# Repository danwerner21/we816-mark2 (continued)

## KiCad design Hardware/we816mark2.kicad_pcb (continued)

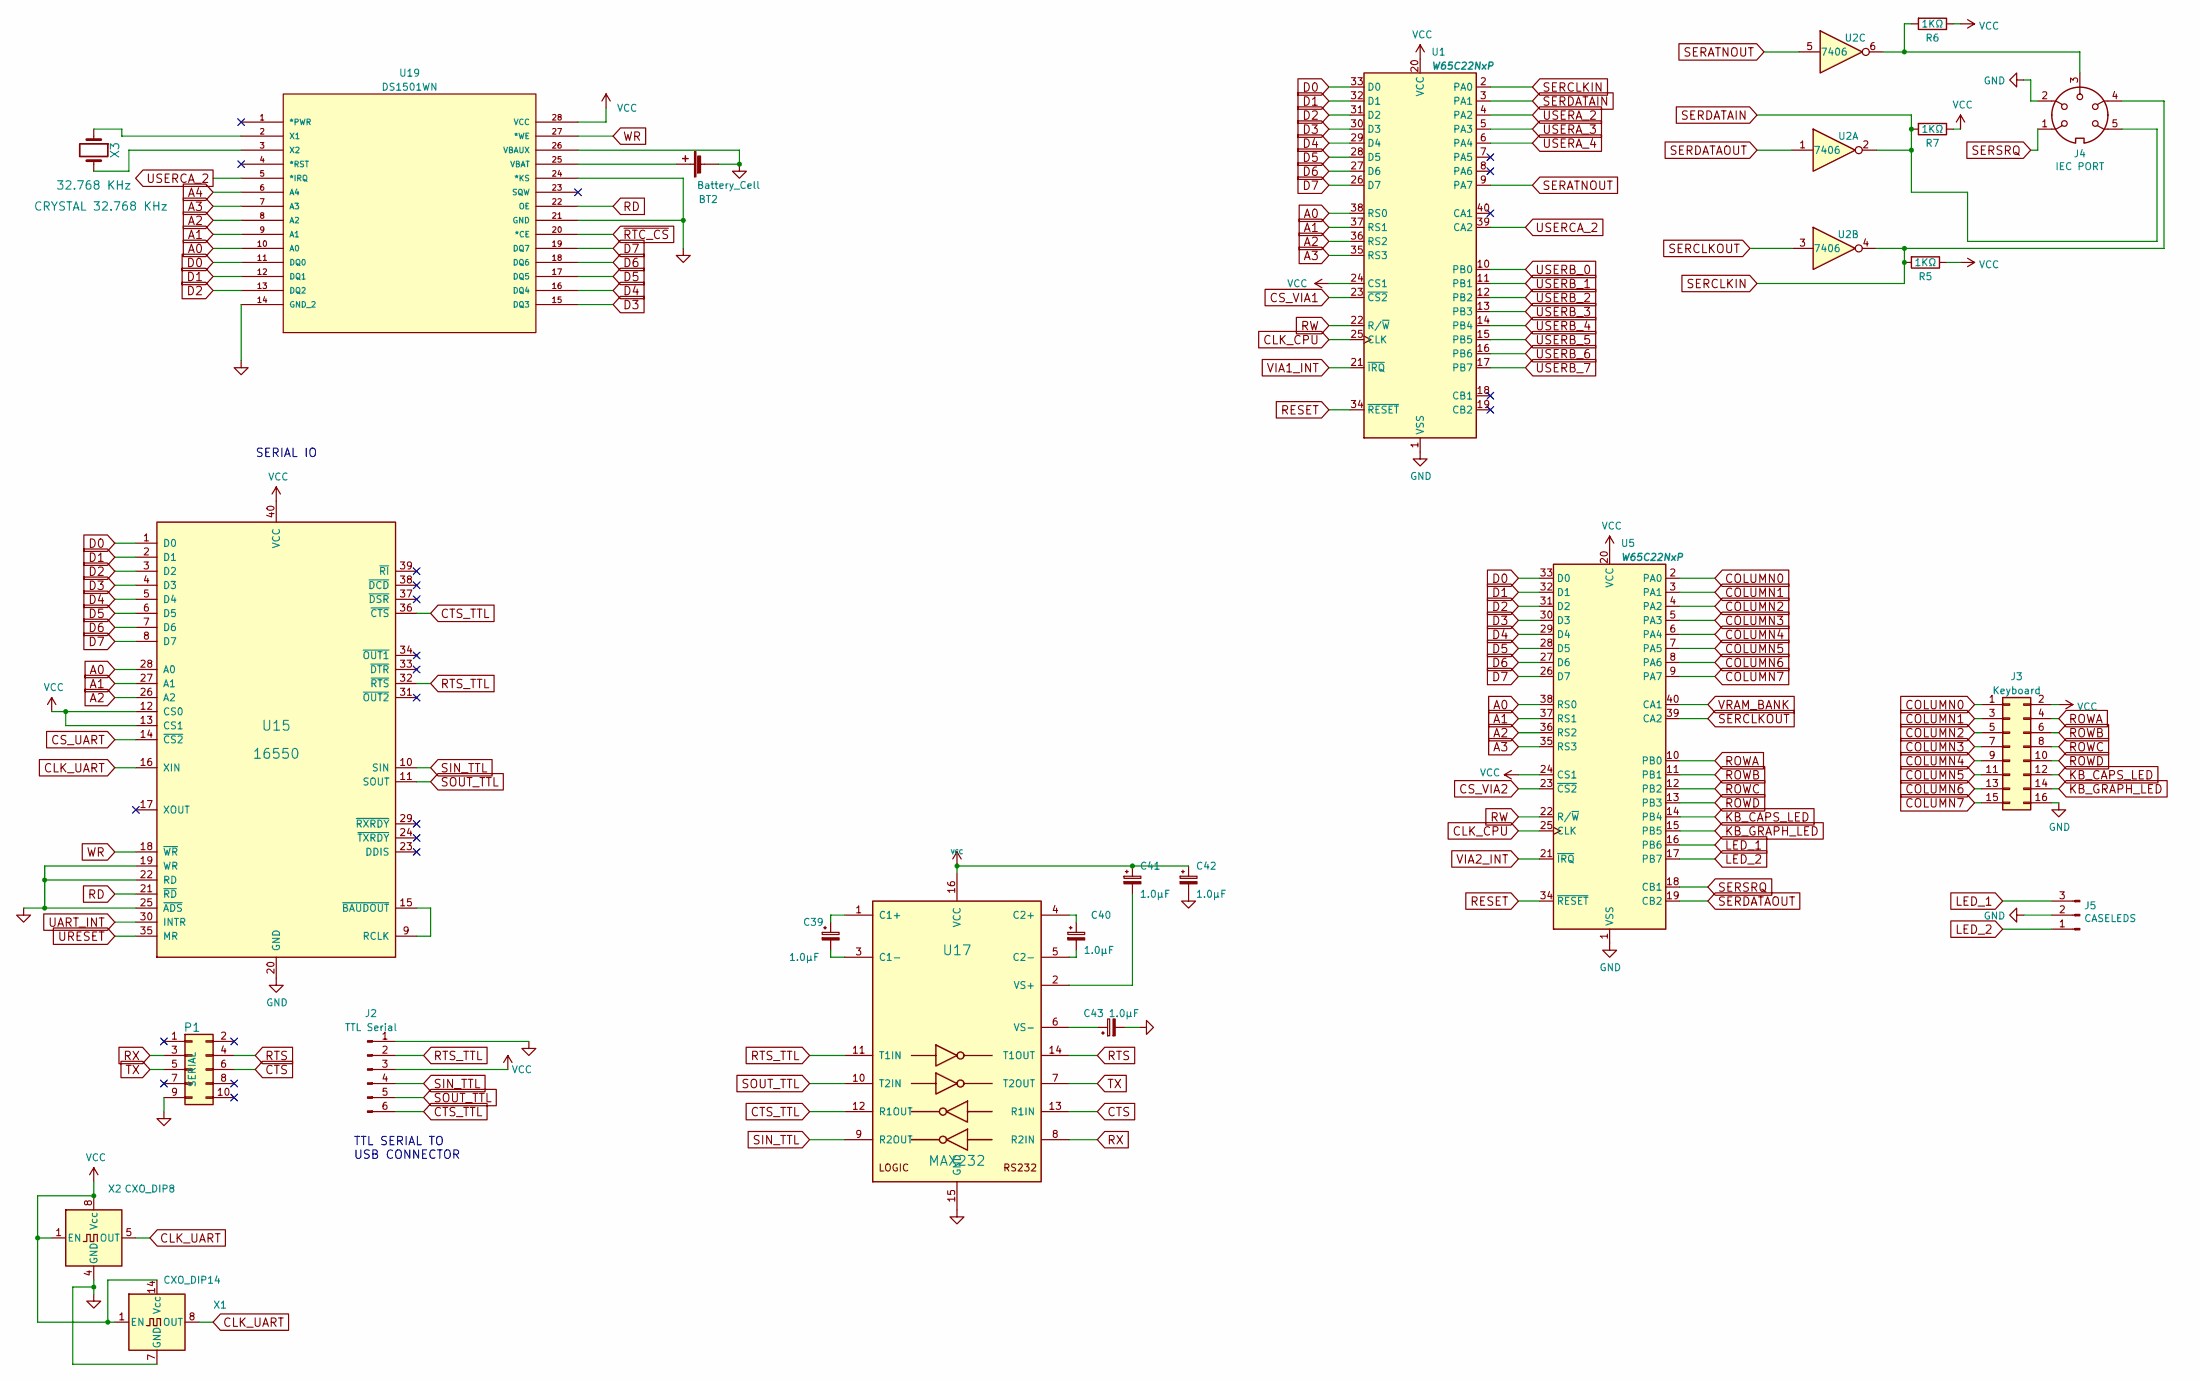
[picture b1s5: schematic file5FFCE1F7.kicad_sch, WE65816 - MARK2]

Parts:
BT2: Battery_Cell; Battery_Holder_Coin_2032_BS-7_FIXED
C39, C40, C41, C42, C43: 1.0µF; CP_Radial_D4.0mm_P2.00mm
J2: TTL Serial; PinHeader_1x06_P2.54mm_Vertical
J3: Keyboard; PinHeader_2x08_P2.54mm_Vertical
J4: IEC PORT; din6
J5: CASELEDS; PinHeader_1x03_P2.54mm_Vertical
P1: SERIAL; PinHeader_2x05_P2.54mm_Vertical
R5, R6, R7: 1KΩ; R_Axial_DIN0204_L3.6mm_D1.6mm_P5.08mm_Horizontal
U1, U5: W65C22NxP; DIP-40_W15.24mm_Socket_LongPads
U2: 7406; DIP-14_W7.62mm_Socket_LongPads
U15: 16550; DIP-40_W15.24mm_Socket_LongPads
U17: MAX232; DIP-16_W7.62mm_Socket_LongPads
U19: DS1501WN; DIP-28_W15.24mm_Socket_LongPads; MANUFACTURER_PART_NUMBER DS1501WN+
X1: CXO_DIP14; Oscillator_DIP-14
X2: CXO_DIP8; Oscillator_DIP-8
X3: CRYSTAL 32.768 KHz; Crystal_Round_D1.5mm_Vertical

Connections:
A0: U1.38 (RS0), U5.38 (RS0), U15.28 (A0), U19.10 (A0); also elsewhere on the board
A1: U1.37 (RS1), U5.37 (RS1), U15.27 (A1), U19.9 (A1); also elsewhere on the board
A2: U1.36 (RS2), U5.36 (RS2), U15.26 (A2), U19.8 (A2); also elsewhere on the board
A3: U1.35 (RS3), U5.35 (RS3), U19.7 (A3); also elsewhere on the board
A4: U19.6 (A4); also elsewhere on the board
COLUMN0: J3.1, U5.2 (PA0)
COLUMN1: J3.3, U5.3 (PA1)
COLUMN2: J3.5, U5.4 (PA2)
COLUMN3: J3.7, U5.5 (PA3)
COLUMN4: J3.9, U5.6 (PA4)
COLUMN5: J3.11, U5.7 (PA5)
COLUMN6: J3.13, U5.8 (PA6)
COLUMN7: J3.15, U5.9 (PA7)
CS_UART: U15.14 (~CS2); also elsewhere on the board
CS_VIA1: U1.23 (~CS2); also elsewhere on the board
CS_VIA2: U5.23 (~CS2); also elsewhere on the board
CTS: P1.6, U17.13 (R1IN)
CTS_TTL: J2.6, U15.36 (~CTS), U17.12 (R1OUT)
D0: U1.33 (D0), U5.33 (D0), U15.1 (D0), U19.11 (DQ0); also elsewhere on the board
D1: U1.32 (D1), U5.32 (D1), U15.2 (D1), U19.12 (DQ1); also elsewhere on the board
D2: U1.31 (D2), U5.31 (D2), U15.3 (D2), U19.13 (DQ2); also elsewhere on the board
D3: U1.30 (D3), U5.30 (D3), U15.4 (D3), U19.15 (DQ3); also elsewhere on the board
D4: U1.29 (D4), U5.29 (D4), U15.5 (D4), U19.16 (DQ4); also elsewhere on the board
D5: U1.28 (D5), U5.28 (D5), U15.6 (D5), U19.17 (DQ5); also elsewhere on the board
D6: U1.27 (D6), U5.27 (D6), U15.7 (D6), U19.18 (DQ6); also elsewhere on the board
D7: U1.26 (D7), U5.26 (D7), U15.8 (D7), U19.19 (DQ7); also elsewhere on the board
GND: BT2.2 (-), C42.2, C43.2, J2.1, J3.16, J4.2, J5.2, P1.9, U1.1 (VSS), U5.1 (VSS), U15.19 (WR), U15.20 (GND), U15.22 (RD), U15.25 (~ADS), U17.15 (GND), U19.14 (GND_2), U19.21 (GND), U19.24 (*KS), U19.26 (VBAUX), X1.7 (GND), X2.4 (GND); also elsewhere on the board
KB_CAPS_LED: J3.12, U5.14 (PB4)
KB_GRAPH_LED: J3.14, U5.15 (PB5)
LED_1: J5.3, U5.16 (PB6)
LED_2: J5.1, U5.17 (PB7)
unnamed: BT2.1 (+), U19.25 (VBAT)
unnamed: J4.3, R6.2, U2.6
unnamed: U15.9 (RCLK), U15.15 (~BAUDOUT)
unnamed: C39.1, U17.1 (C1+)
unnamed: C39.2, U17.3 (C1-)
unnamed: C40.1, U17.4 (C2+)
unnamed: C40.2, U17.5 (C2-)
unnamed: C41.2, U17.2 (VS+)
unnamed: C43.1, U17.6 (VS-)
unnamed: U19.2 (X1), X3.1
unnamed: U19.3 (X2), X3.2
RD: U15.21 (~RD), U19.22 (OE); also elsewhere on the board
RESET: U1.34 (~RESET), U5.34 (~RESET); also elsewhere on the board
ROWA: J3.4, U5.10 (PB0)
ROWB: J3.6, U5.11 (PB1)
ROWC: J3.8, U5.12 (PB2)
ROWD: J3.10, U5.13 (PB3)
RTS: P1.4, U17.14 (T1OUT)
RTS_TTL: J2.2, U15.32 (~RTS), U17.11 (T1IN)
RW: U1.22 (R/~W), U5.22 (R/~W); also elsewhere on the board
RX: P1.3, U17.8 (R2IN)
SERATNOUT: U1.9 (PA7), U2.5
SERCLKIN: J4.4, R5.2, U1.2 (PA0), U2.4
SERCLKOUT: U2.3, U5.39 (CA2)
SERDATAIN: J4.5, R7.2, U1.3 (PA1), U2.2
SERDATAOUT: U2.1, U5.19 (CB2)
SERSRQ: J4.1, U5.18 (CB1)
SIN_TTL: J2.4, U15.10 (SIN), U17.9 (R2OUT)
SOUT_TTL: J2.5, U15.11 (SOUT), U17.10 (T2IN)
TX: P1.5, U17.7 (T2OUT)
UART_INT: U15.30 (INTR); also elsewhere on the board
URESET: U15.35 (MR); also elsewhere on the board
USERA_2: U1.4 (PA2); also elsewhere on the board
USERA_3: U1.5 (PA3); also elsewhere on the board
USERA_4: U1.6 (PA4); also elsewhere on the board
USERB_0: U1.10 (PB0); also elsewhere on the board
USERB_1: U1.11 (PB1); also elsewhere on the board
USERB_2: U1.12 (PB2); also elsewhere on the board
USERB_3: U1.13 (PB3); also elsewhere on the board
USERB_4: U1.14 (PB4); also elsewhere on the board
USERB_5: U1.15 (PB5); also elsewhere on the board
USERB_6: U1.16 (PB6); also elsewhere on the board
USERB_7: U1.17 (PB7); also elsewhere on the board
USERCA_2: U1.39 (CA2), U19.5 (*IRQ)
VCC: C41.1, C42.1, J2.3, J3.2, R5.1, R6.1, R7.1, U1.20 (VCC), U1.24 (CS1), U5.20 (VCC), U5.24 (CS1), U15.12 (CS0), U15.13 (CS1), U15.40 (VCC), U17.16 (VCC), U19.28 (VCC), X1.1 (EN), X1.14 (Vcc), X2.1 (EN), X2.8 (Vcc); also elsewhere on the board
VIA1_INT: U1.21 (~IRQ); also elsewhere on the board
VIA2_INT: U5.21 (~IRQ); also elsewhere on the board
VRAM_BANK: U5.40 (CA1); also elsewhere on the board
WR: U15.18 (~WR), U19.27 (*WE); also elsewhere on the board
~RTC_CS: U19.20 (*CE); also elsewhere on the board

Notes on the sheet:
TTL SERIAL TO USB CONNECTOR
SERIAL IO

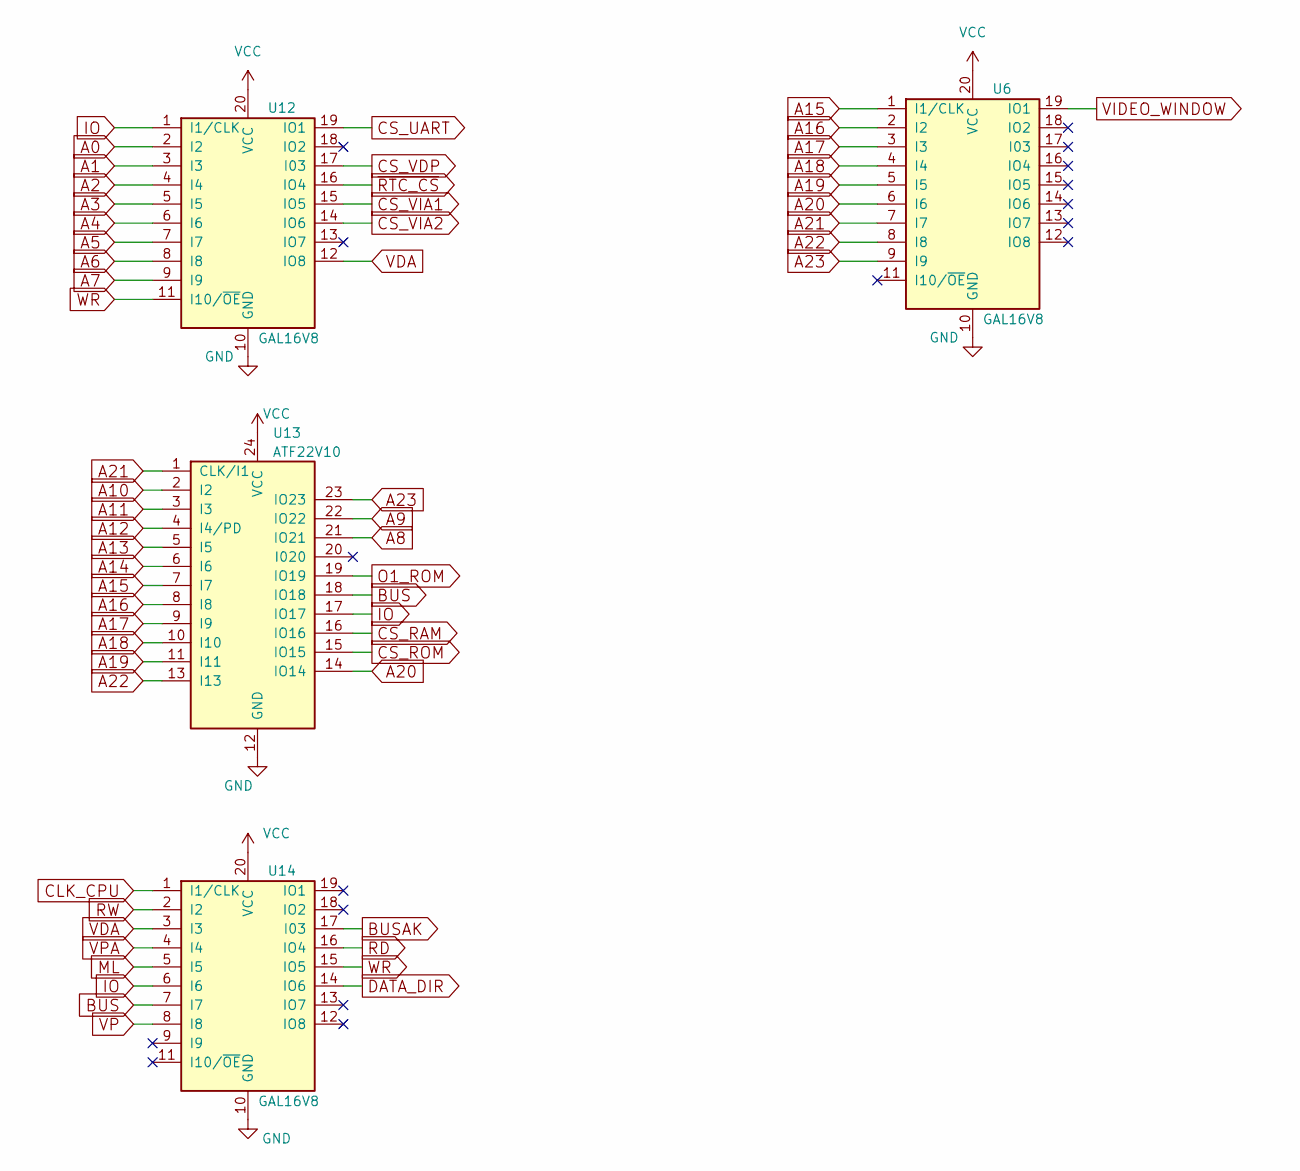
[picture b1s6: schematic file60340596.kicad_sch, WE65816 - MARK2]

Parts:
U6, U12, U14: GAL16V8; DIP-20_W7.62mm_Socket_LongPads
U13: ATF22V10; DIP-24_W7.62mm_Socket_LongPads

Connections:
A0: U12.2 (I2); also elsewhere on the board
A1: U12.3 (I3); also elsewhere on the board
A2: U12.4 (I4); also elsewhere on the board
A3: U12.5 (I5); also elsewhere on the board
A4: U12.6 (I6); also elsewhere on the board
A5: U12.7 (I7); also elsewhere on the board
A6: U12.8 (I8); also elsewhere on the board
A7: U12.9 (I9); also elsewhere on the board
A8: U13.21 (IO21); also elsewhere on the board
A9: U13.22 (IO22); also elsewhere on the board
A10: U13.2 (I2); also elsewhere on the board
A11: U13.3 (I3); also elsewhere on the board
A12: U13.4 (I4/PD); also elsewhere on the board
A13: U13.5 (I5); also elsewhere on the board
A14: U13.6 (I6); also elsewhere on the board
A15: U6.1 (I1/CLK), U13.7 (I7); also elsewhere on the board
A16: U6.2 (I2), U13.8 (I8); also elsewhere on the board
A17: U6.3 (I3), U13.9 (I9); also elsewhere on the board
A18: U6.4 (I4), U13.10 (I10); also elsewhere on the board
A19: U6.5 (I5), U13.11 (I11); also elsewhere on the board
A20: U6.6 (I6), U13.14 (IO14); also elsewhere on the board
A21: U6.7 (I7), U13.1 (CLK/I1); also elsewhere on the board
A22: U6.8 (I8), U13.13 (I13); also elsewhere on the board
A23: U6.9 (I9), U13.23 (IO23); also elsewhere on the board
BUS: U13.18 (IO18), U14.7 (I7)
BUSAK: U14.17 (I03); also elsewhere on the board
CS_RAM: U13.16 (IO16); also elsewhere on the board
CS_ROM: U13.15 (IO15); also elsewhere on the board
CS_UART: U12.19 (IO1); also elsewhere on the board
CS_VDP: U12.17 (I03); also elsewhere on the board
CS_VIA1: U12.15 (IO5); also elsewhere on the board
CS_VIA2: U12.14 (IO6); also elsewhere on the board
DATA_DIR: U14.14 (IO6); also elsewhere on the board
GND: U6.10 (GND), U12.10 (GND), U13.12 (GND), U14.10 (GND); also elsewhere on the board
IO: U12.1 (I1/CLK), U13.17 (IO17), U14.6 (I6)
ML: U14.5 (I5); also elsewhere on the board
O1_ROM: U13.19 (IO19); also elsewhere on the board
RD: U14.16 (IO4); also elsewhere on the board
RW: U14.2 (I2); also elsewhere on the board
VCC: U6.20 (VCC), U12.20 (VCC), U13.24 (VCC), U14.20 (VCC); also elsewhere on the board
VDA: U12.12 (IO8), U14.3 (I3); also elsewhere on the board
VIDEO_WINDOW: U6.19 (IO1); also elsewhere on the board
VP: U14.8 (I8); also elsewhere on the board
VPA: U14.4 (I4); also elsewhere on the board
WR: U12.11 (I10/~OE), U14.15 (IO5); also elsewhere on the board
~RTC_CS: U12.16 (IO4); also elsewhere on the board

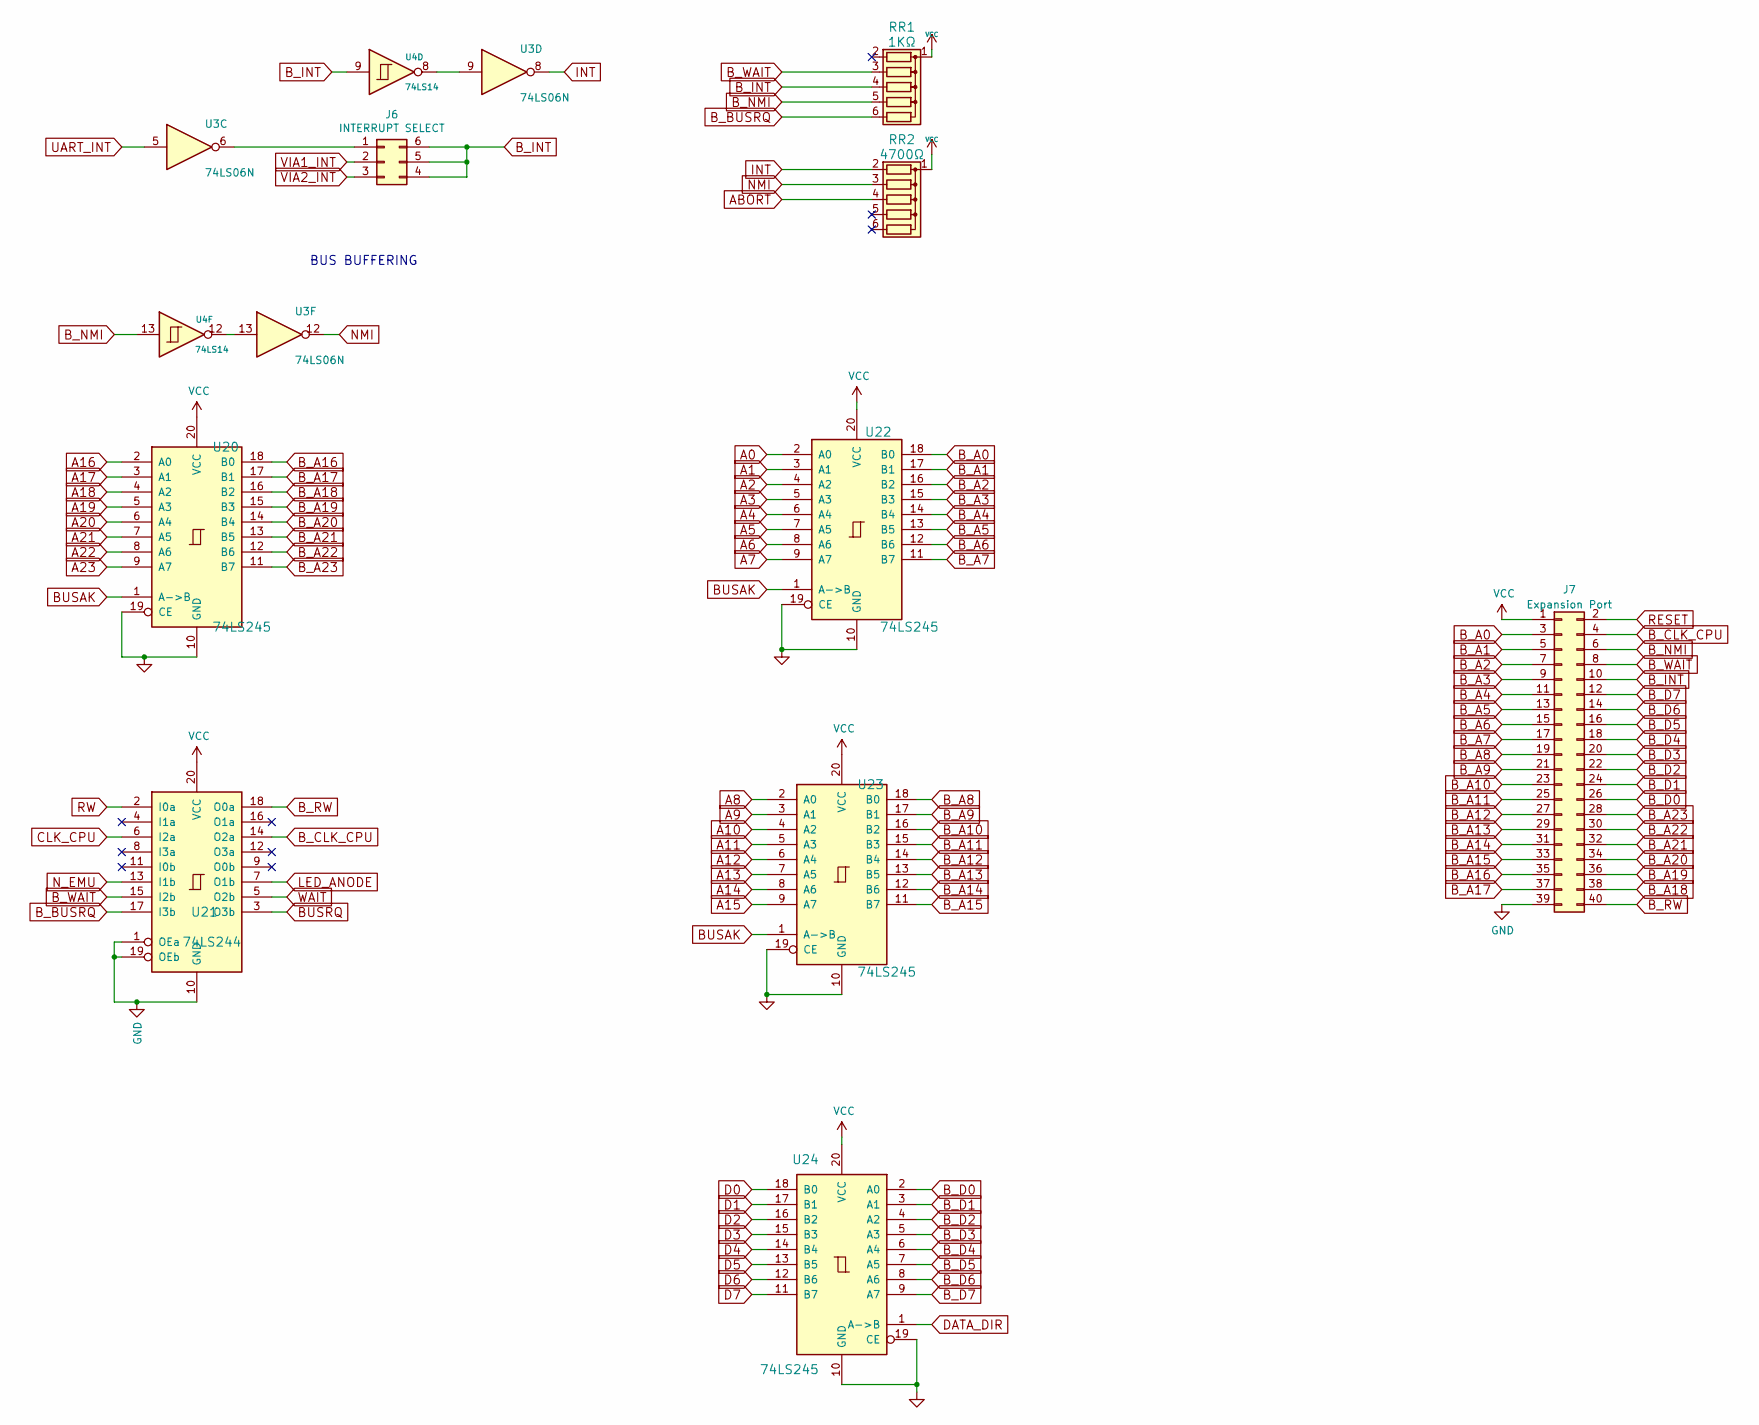
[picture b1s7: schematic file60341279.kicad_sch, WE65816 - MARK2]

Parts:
J6: INTERRUPT SELECT; PinHeader_2x04_P2.54mm_Vertical
J7: Expansion Port; PinSocket_2x20_P2.54mm_Horizontal
RR1: 1KΩ; R_Array_SIP6
RR2: 4700Ω; R_Array_SIP6
U3: 74LS06N; DIP-14_W7.62mm_Socket_LongPads
U4: 74LS14; DIP-14_W7.62mm_Socket_LongPads
U20, U22, U23, U24: 74LS245; DIP-20_W7.62mm_Socket_LongPads
U21: 74LS244; DIP-20_W7.62mm_Socket_LongPads

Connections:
A0: U22.2 (A0); also elsewhere on the board
A1: U22.3 (A1); also elsewhere on the board
A2: U22.4 (A2); also elsewhere on the board
A3: U22.5 (A3); also elsewhere on the board
A4: U22.6 (A4); also elsewhere on the board
A5: U22.7 (A5); also elsewhere on the board
A6: U22.8 (A6); also elsewhere on the board
A7: U22.9 (A7); also elsewhere on the board
A8: U23.2 (A0); also elsewhere on the board
A9: U23.3 (A1); also elsewhere on the board
A10: U23.4 (A2); also elsewhere on the board
A11: U23.5 (A3); also elsewhere on the board
A12: U23.6 (A4); also elsewhere on the board
A13: U23.7 (A5); also elsewhere on the board
A14: U23.8 (A6); also elsewhere on the board
A15: U23.9 (A7); also elsewhere on the board
A16: U20.2 (A0); also elsewhere on the board
A17: U20.3 (A1); also elsewhere on the board
A18: U20.4 (A2); also elsewhere on the board
A19: U20.5 (A3); also elsewhere on the board
A20: U20.6 (A4); also elsewhere on the board
A21: U20.7 (A5); also elsewhere on the board
A22: U20.8 (A6); also elsewhere on the board
A23: U20.9 (A7); also elsewhere on the board
ABORT: RR2.4 (R3); also elsewhere on the board
BUSAK: U20.1 (A->B), U22.1 (A->B), U23.1 (A->B); also elsewhere on the board
BUSRQ: U21.3 (O3b); also elsewhere on the board
B_A0: J7.3, U22.18 (B0)
B_A1: J7.5, U22.17 (B1)
B_A2: J7.7, U22.16 (B2)
B_A3: J7.9, U22.15 (B3)
B_A4: J7.11, U22.14 (B4)
B_A5: J7.13, U22.13 (B5)
B_A6: J7.15, U22.12 (B6)
B_A7: J7.17, U22.11 (B7)
B_A8: J7.19, U23.18 (B0)
B_A9: J7.21, U23.17 (B1)
B_A10: J7.23, U23.16 (B2)
B_A11: J7.25, U23.15 (B3)
B_A12: J7.27, U23.14 (B4)
B_A13: J7.29, U23.13 (B5)
B_A14: J7.31, U23.12 (B6)
B_A15: J7.33, U23.11 (B7)
B_A16: J7.35, U20.18 (B0)
B_A17: J7.37, U20.17 (B1)
B_A18: J7.38, U20.16 (B2)
B_A19: J7.36, U20.15 (B3)
B_A20: J7.34, U20.14 (B4)
B_A21: J7.32, U20.13 (B5)
B_A22: J7.30, U20.12 (B6)
B_A23: J7.28, U20.11 (B7)
B_BUSRQ: RR1.6 (R5), U21.17 (I3b)
B_CLK_CPU: J7.4, U21.14 (O2a)
B_D0: J7.26, U24.2 (A0)
B_D1: J7.24, U24.3 (A1)
B_D2: J7.22, U24.4 (A2)
B_D3: J7.20, U24.5 (A3)
B_D4: J7.18, U24.6 (A4)
B_D5: J7.16, U24.7 (A5)
B_D6: J7.14, U24.8 (A6)
B_D7: J7.12, U24.9 (A7)
B_INT: J6.4, J6.5, J6.6, J7.10, RR1.4 (R3), U4.9
B_NMI: J7.6, RR1.5 (R4), U4.13
B_RW: J7.40, U21.18 (O0a)
B_WAIT: J7.8, RR1.3 (R2), U21.15 (I2b)
D0: U24.18 (B0); also elsewhere on the board
D1: U24.17 (B1); also elsewhere on the board
D2: U24.16 (B2); also elsewhere on the board
D3: U24.15 (B3); also elsewhere on the board
D4: U24.14 (B4); also elsewhere on the board
D5: U24.13 (B5); also elsewhere on the board
D6: U24.12 (B6); also elsewhere on the board
D7: U24.11 (B7); also elsewhere on the board
DATA_DIR: U24.1 (A->B); also elsewhere on the board
GND: J7.39, U20.10 (GND), U20.19 (CE), U21.1 (OEa), U21.10 (GND), U21.19 (OEb), U22.10 (GND), U22.19 (CE), U23.10 (GND), U23.19 (CE), U24.10 (GND), U24.19 (CE); also elsewhere on the board
INT: RR2.2 (R1), U3.8; also elsewhere on the board
LED_ANODE: U21.7 (O1b); also elsewhere on the board
NMI: RR2.3 (R2), U3.12; also elsewhere on the board
N_EMU: U21.13 (I1b); also elsewhere on the board
unnamed: J6.1, U3.6
unnamed: U3.9, U4.8
unnamed: U3.13, U4.12
RESET: J7.2; also elsewhere on the board
RW: U21.2 (I0a); also elsewhere on the board
UART_INT: U3.5; also elsewhere on the board
VCC: J7.1, RR1.1 (common), RR2.1 (common), U20.20 (VCC), U21.20 (VCC), U22.20 (VCC), U23.20 (VCC), U24.20 (VCC); also elsewhere on the board
VIA1_INT: J6.2; also elsewhere on the board
VIA2_INT: J6.3; also elsewhere on the board
WAIT: U21.5 (O2b); also elsewhere on the board

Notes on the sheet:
BUS BUFFERING

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
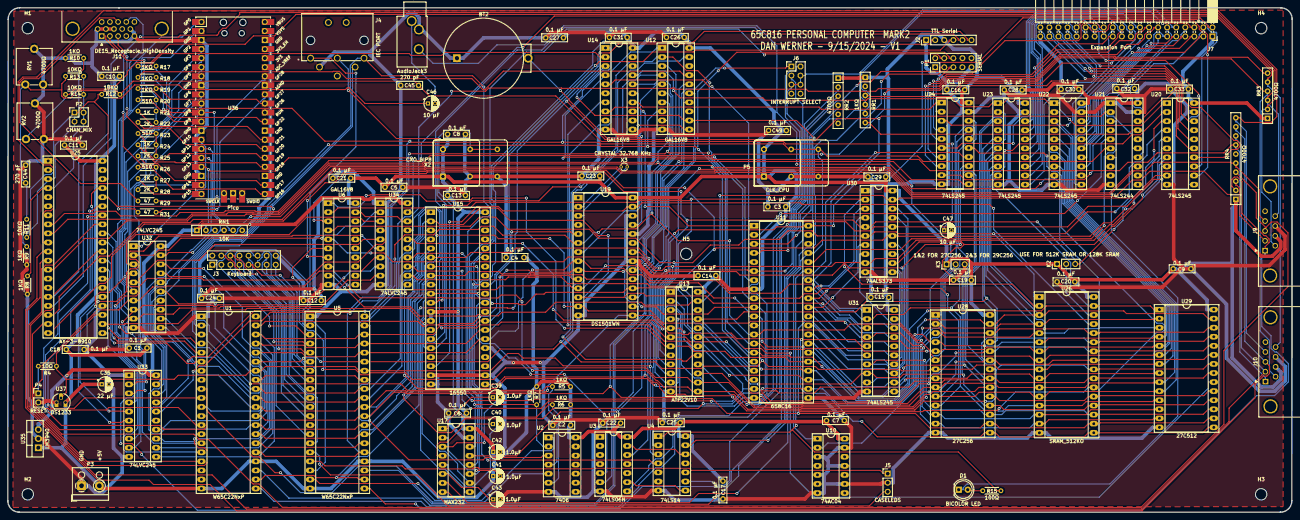
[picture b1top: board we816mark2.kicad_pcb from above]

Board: 2 copper layers, 360.1 x 141.4 mm, 136 parts (0 on the bottom side), 228 nets.

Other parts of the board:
X4: CXO_DIP14; Oscillator_DIP-14

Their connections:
GND: X4.7 (GND); also elsewhere on the board
VCC: X4.1 (EN), X4.14 (Vcc); also elsewhere on the board

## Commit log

2024-07-15 initial
2024-07-17 mark 2 work
2024-07-20 pcb work
2024-08-11 initial pico firmware
2024-08-11 graphics work
2024-08-18 BASIC work
2024-08-18 Rename AY38910.asm to ay38910.asm
2024-08-18 Rename diskcmds.ASM to diskcmds.asm
2024-08-18 Rename screencmds.ASM to screencmds.asm
2024-08-18 Rename ZEROPAGE.ASM to zeropage.asm
2024-08-18 Rename TOKENS.ASM to tokens.asm
2024-08-18 Rename NUMCONST.ASM to numconst.asm
2024-08-18 Rename MESSAGES.ASM to messages.asm
2024-08-18 Rename IOVECT.ASM to iovect.asm
2024-08-18 Rename BASIC/ay38910.asm to Bay38910.asm
2024-08-18 Rename BASIC/dbasic816.asm to Bdbasic816.asm
2024-08-18 Rename BASIC/zeropage.asm to Bzeropage.asm
2024-08-18 Rename BASIC/definitions.asm to Bdefinitions.asm
2024-08-18 Rename BASIC/diskcmds.asm to Bdiskcmds.asm
2024-08-18 Rename BASIC/iovect.asm to Biovect.asm
2024-08-18 Rename BASIC/messages.asm to Bmessages.asm
2024-08-18 Rename BASIC/numconst.asm to Bnumconst.asm
2024-08-18 Rename BASIC/screencmds.asm to Bscreencmds.asm
2024-08-18 Rename BASIC/tokens.asm to Btokens.asm
2024-08-18 Rename BASIC/.vs/BASIC/v17/.suo to B.suo
2024-08-18 Rename BASIC/.vs/slnx.sqlite to Bslnx.sqlite
2024-08-18 Rename firmware/CONSERIAL.ASM to fCONSERIAL.ASM
2024-08-18 Rename firmware/IEC.asm to fIEC.asm
2024-08-18 Rename firmware/ROMBIOS816.LST to fROMBIOS816.LST
2024-08-18 Rename firmware/ROMBIOS816.asm to fiROMBIOS816.asm
2024-08-18 Rename firmware/ROMBIOS816.hex to fiROMBIOS816.hex
2024-08-18 Rename firmware/ROMBIOS816.map to fiROMBIOS816.map
2024-08-18 clean up
2024-08-18 add binary output
2024-08-24 fix GAL error
2024-08-24 work on BASIC screen editor
2024-08-28 relocate rom
2024-09-01 add 80 col support
2024-09-02 BASIC graphics work
2024-09-02 add plot commands to BASIC
2024-09-02 doc updates
2024-09-07 rtc updates
2024-09-16 add basic RTC functions
2024-09-16 documentation updates
2025-02-02 bug fixes
